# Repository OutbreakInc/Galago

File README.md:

Static sites are the fixies of the Internet.
      -Paul Graham, @paulg

Want to know how this works?  Fixie magic.

View the site here: [Logiblock.com](http://logiblock.com)

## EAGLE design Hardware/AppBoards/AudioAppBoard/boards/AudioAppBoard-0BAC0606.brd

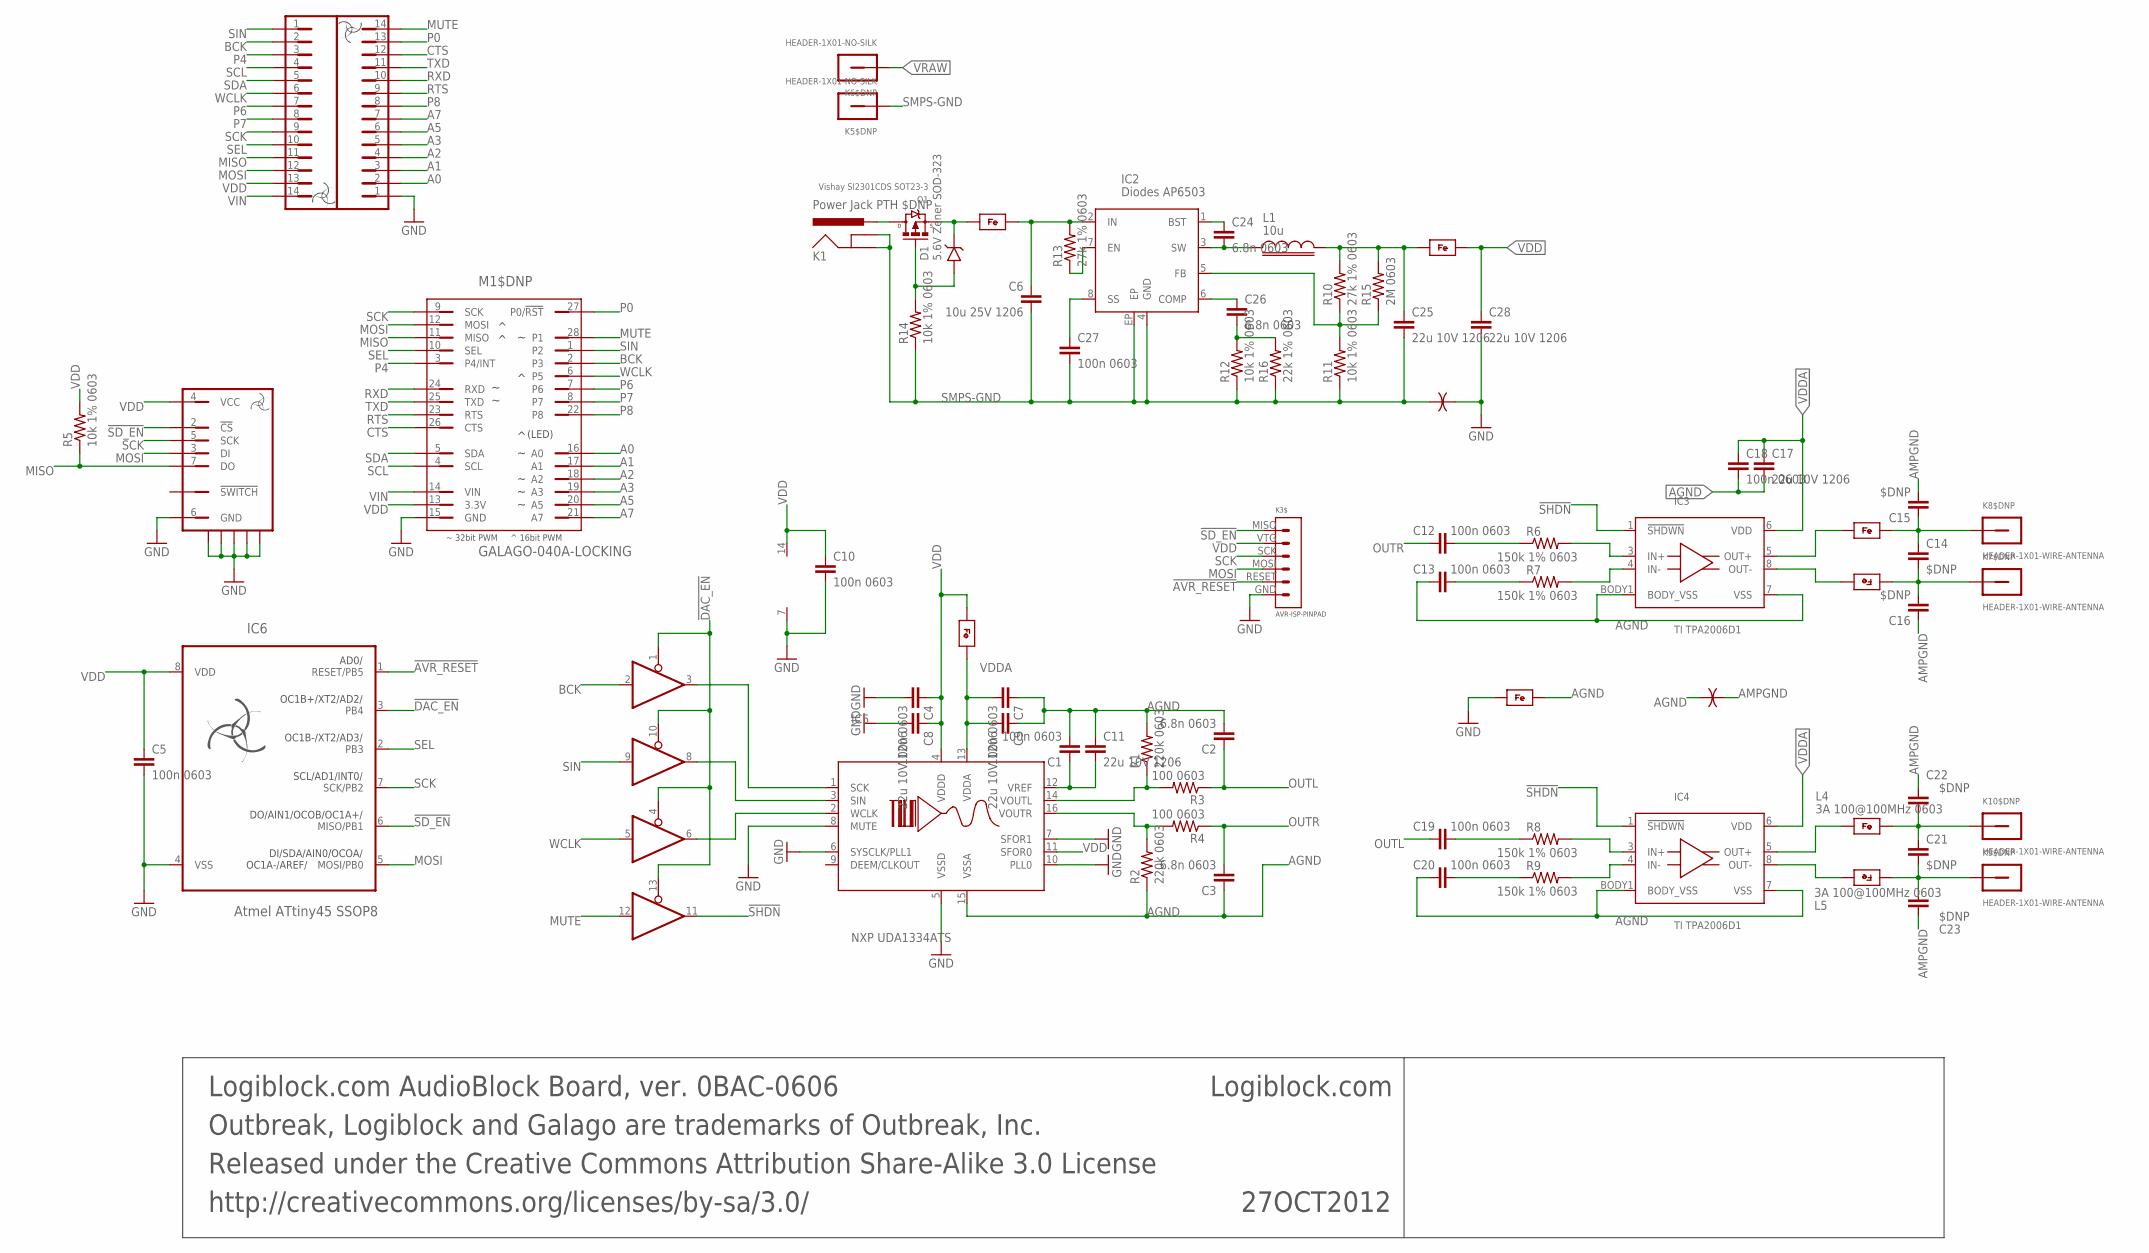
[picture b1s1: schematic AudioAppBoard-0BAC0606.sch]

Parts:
27OCT2012: Logiblock.com AudioBlock Board, ver. 0BAC-0606; INFO-BLOCK
C1, C4, C5, C7, C10: 100n 0603; 0603
C2, C3: 6.8n 0603; 0603
C6: 10u 25V 1206; 1206
C8, C9, C11, C17, C25, C28: 22u 10V 1206; 1206
C12, C13, C18, C19, C20, C27: 100n 0603; 0603-MIN
C14, C15, C16, C21, C22, C23: $DNP; 0603-MIN
C24, C26: 6.8n 0603; 0603-MIN
D1: 5.6V Zener SOD-323; SOD323
FB1, FB2, FB3: 3A 100@100MHz 0603; 0603
FB4: 3A 100@100MHz 0603; 0603-MIN
IC1: 74HC125-TSSOP14; TSSOP14
IC2: Diodes AP6503; EIAJ-SOIC8-3.9MM-EXPOSED-PAD
IC3, IC4: TI TPA2006D1; QFN8-3X3MM-TI-TPA200X
IC5: NXP UDA1334ATS; TSSOP16
IC6: Atmel ATtiny45 SSOP8; TSSOP8-4.4MM
K1: Power Jack PTH $DNP; POWER_JACK_PTH
K2: HIROSE-DM3D-SF-MICROSD; HIROSE-MICROSD-SOCKET-DM3D-SF
K2$DNP, K4$DNP: HEADER-1X14-NO-SILK-CHUNKY
K3$: AVR-ISP-PINPAD
K5$DNP, K6$DNP: HEADER-1X01-NO-SILK
K7$DNP, K8$DNP, K9$DNP, K10$DNP: HEADER-1X01-WIRE-ANTENNA
L1: 10u; INDUCTOR-SMD-6X6MM
L2, L3, L4, L5: 3A 100@100MHz 0603; 0603-MIN
M1$DNP: GALAGO-040A-LOCKING; GALAGO-LOCKING
Q1: Vishay SI2301CDS SOT23-3; SOT23-3
R1, R2: 220k 0603; 0603
R3, R4: 100 0603; 0603
R5, R11, R12, R14: 10k 1% 0603; 0603-MIN
R6, R7, R8, R9: 150k 1% 0603; 0603-MIN
R10, R13: 27k 1% 0603; 0603-MIN
R15: 2M 0603; 0603-MIN
R16: 22k 1% 0603; 0603-MIN
U1$, U2$: GND-ISOLATOR-0.008"

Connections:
!AVR_RESET: IC6.1 (RESET/PB5), K3$.RESET
!DAC_EN: IC1.1 (EN), IC1.4 (EN), IC1.10 (EN), IC1.13 (EN), IC6.3 (PB4)
!SD_EN: IC6.6 (MISO/PB1), K2.2 (!CS), K3$.MISO
!SHDN: IC1.11 (Y), IC3.1 (!SHDWN), IC4.1 (!SHDWN)
A0: K4$DNP.2, M1$DNP.16 (A0)
A1: K4$DNP.3, M1$DNP.17 (A1)
A2: K4$DNP.4, M1$DNP.18 (A2)
A3: K4$DNP.5, M1$DNP.19 (A3)
A5: K4$DNP.6, M1$DNP.20 (A5)
A7: K4$DNP.7, M1$DNP.21 (A7)
AGND: C1.1, C2.1, C3.2, C7.2, C9.2, C11.2, C13.2, C17.1, C18.1, C20.2, FB4.2, IC3.7 (VSS), IC3.BODY1 (BODY_VSS), IC4.7 (VSS), IC4.BODY1 (BODY_VSS), IC5.15 (VSSA), R1.2, R2.1, U2$.1 (A)
AMPGND: C15.1, C16.2, C22.1, C23.2, U2$.2 (B)
BCK: IC1.2 (A), K2$DNP.2, M1$DNP.2 (P3)
CTS: K4$DNP.12, M1$DNP.26 (CTS)
DAC_SCK: IC1.3 (Y), IC5.1 (SCK)
DAC_SIN: IC1.8 (Y), IC5.3 (SIN)
DAC_WCLK: IC1.6 (Y), IC5.2 (WCLK)
GND: C4.1, C5.1, C8.1, C10.1, C28.1, FB4.1, IC1.7 (VSS), IC5.5 (VSSD), IC5.6 (SYSCLK/PLL1), IC5.7 (SFOR1), IC5.8 (MUTE), IC5.10 (PLL0), IC6.4 (VSS), K2.6 (GND), K2.PP$1, K2.PP$2, K2.PP$3, K2.PP$4, K2.PP$5, K3$.GND, K4$DNP.1, M1$DNP.15 (GND), U1$.2 (B)
MISO: K2.7 (DO), K2$DNP.11, M1$DNP.11 (MISO), R5.1
MOSI: IC6.5 (MOSI/PB0), K2.3 (DI), K2$DNP.12, K3$.MOSI, M1$DNP.12 (MOSI)
MUTE: IC1.12 (A), K4$DNP.14, M1$DNP.28 (P1)
unnamed: C14.2, C15.2, K8$DNP.1, L2.2
unnamed: IC4.5 (OUT+), L4.1
unnamed: IC3.5 (OUT+), L2.1
unnamed: IC3.8 (OUT-), L3.2
unnamed: C12.1, R6.1
unnamed: D1.A, Q1.1 (GATE), R14.2
unnamed: C13.1, R7.1
unnamed: IC3.4 (IN-), R7.2
unnamed: IC3.3 (IN+), R6.2
unnamed: C14.1, C16.1, K7$DNP.1, L3.1
unnamed: IC4.8 (OUT-), L5.2
unnamed: C19.1, R8.1
unnamed: C20.1, R9.1
unnamed: IC4.4 (IN-), R9.2
unnamed: IC4.3 (IN+), R8.2
unnamed: C21.2, C22.2, K10$DNP.1, L4.2
unnamed: C21.1, C23.1, K9$DNP.1, L5.1
unnamed: D1.K, FB1.1, Q1.2 (SOURCE)
unnamed: C26.1, R12.2, R16.2
OUTL: C2.2, C19.2, R3.1
OUTR: C3.1, C12.2, R4.1
P0: K4$DNP.13, M1$DNP.27 (P0/!RST)
P4: K2$DNP.3, M1$DNP.3 (P4/INT)
P6: K2$DNP.7, M1$DNP.7 (P6)
P7: K2$DNP.8, M1$DNP.8 (P7)
P8: K4$DNP.8, M1$DNP.22 (P8)
RTS: K4$DNP.9, M1$DNP.23 (RTS)
RXD: K4$DNP.10, M1$DNP.24 (RXD)
SCK: IC6.7 (SCK/PB2), K2.5 (SCK), K2$DNP.9, K3$.SCK, M1$DNP.9 (SCK)
SCL: K2$DNP.4, M1$DNP.4 (SCL)
SDA: K2$DNP.5, M1$DNP.5 (SDA)
SEL: IC6.2 (PB3), K2$DNP.10, M1$DNP.10 (SEL)
SIN: IC1.9 (A), K2$DNP.1, M1$DNP.1 (P2)
SMPS-BST: C24.2, IC2.1 (BST)
SMPS-COMP: C26.2, IC2.6 (COMP)
SMPS-EN: IC2.7 (EN), R13.1
SMPS-FB: IC2.5 (FB), R10.1, R11.2, R15.1
SMPS-GND: C6.1, C25.1, C27.1, IC2.4 (GND), IC2.EP, K1.GND, K1.GNDBREAK, K5$DNP.1, R11.1, R12.1, R14.1, R16.1, U1$.1 (A)
SMPS-IN: C6.2, FB1.2, IC2.2 (IN), R13.2
SMPS-OUT: C25.2, FB2.1, L1.2, R10.2, R15.2
SMPS-SS: C27.2, IC2.8 (SS)
SMPS-SW: C24.1, IC2.3 (SW), L1.1
TXD: K4$DNP.11, M1$DNP.25 (TXD)
VDD: C4.2, C5.2, C8.2, C10.2, C28.2, FB2.2, FB3.1, IC1.14 (VDD), IC5.4 (VDDD), IC5.11 (SFOR0), IC6.8 (VDD), K2.4 (VCC), K2$DNP.13, K3$.VTG, M1$DNP.13 (3.3V), R5.2
VDDA: C7.1, C9.1, C17.2, C18.2, FB3.2, IC3.6 (VDD), IC4.6 (VDD), IC5.13 (VDDA)
VIN: K2$DNP.14, M1$DNP.14 (VIN)
VOUTL: IC5.14 (VOUTL), R1.1, R3.2
VOUTR: IC5.16 (VOUTR), R2.2, R4.2
VRAW: K1.PWR, K6$DNP.1, Q1.3 (DRAIN)
VREF: C1.2, C11.1, IC5.12 (VREF)
WCLK: IC1.5 (A), K2$DNP.6, M1$DNP.6 (P5)

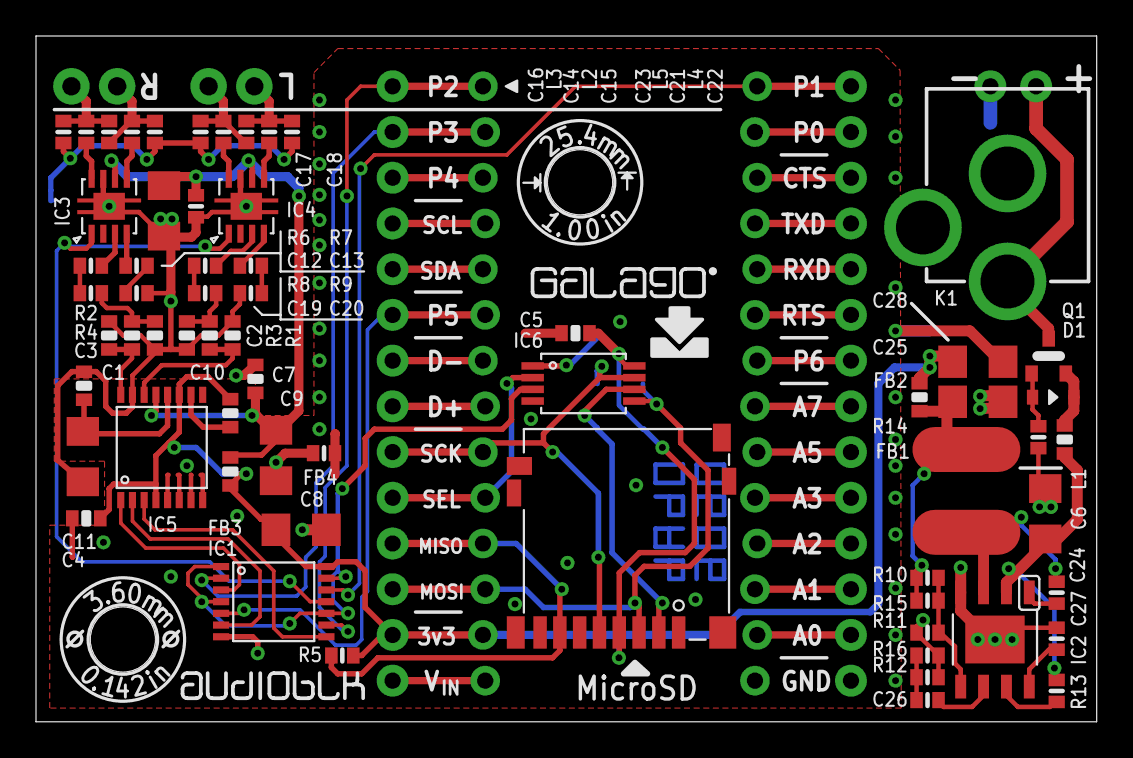
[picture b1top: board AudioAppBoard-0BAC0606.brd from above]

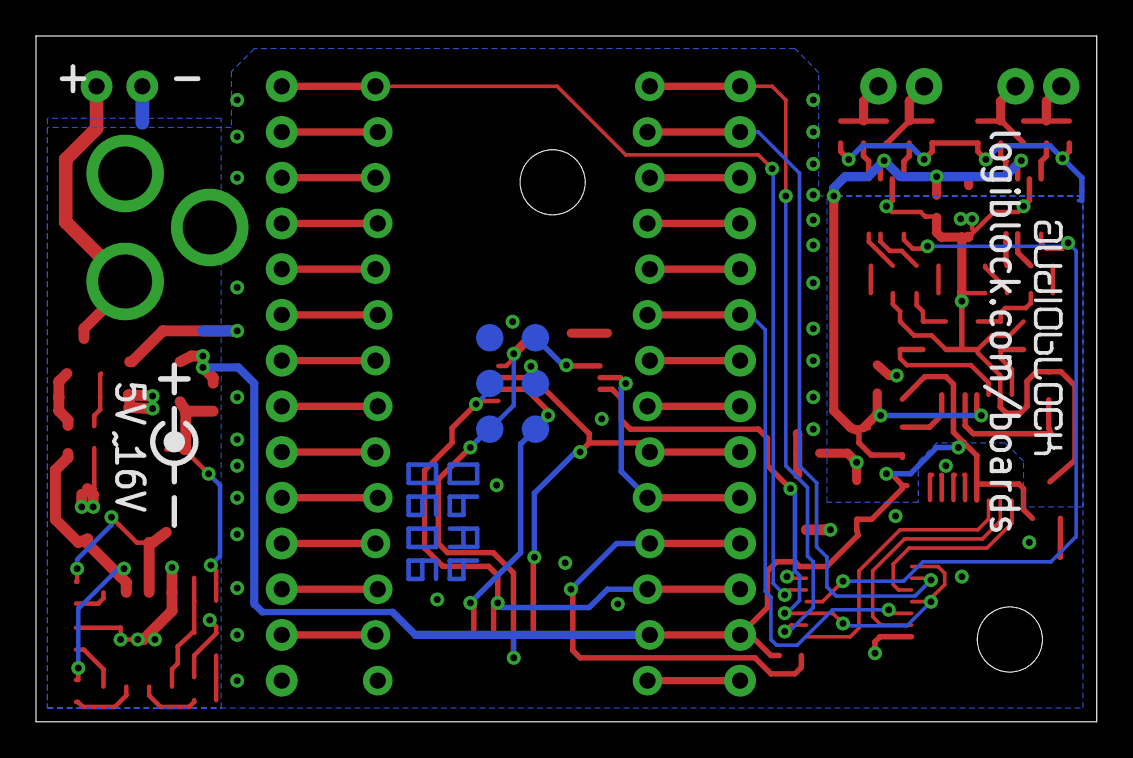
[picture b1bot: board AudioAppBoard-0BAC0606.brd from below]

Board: 2 copper layers, 58.9 x 38.1 mm, 80 parts (3 on the bottom side), 72 nets.

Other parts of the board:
U$1: GALAGO-LOGO
U$3: GALAGO-APP-BOARD-SYMBOL
U$10: MOUNTING-HOLE-3.6MM-LABELLED-DIAM
U$11: MOUNTING-HOLE-3.6MM-LABELLED-DISTANCE

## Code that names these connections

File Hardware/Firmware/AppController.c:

///////////////////////////////////////////////////////////////////////////////////////////


///////////////////////////////////////////////////////////////////////////////////////////

#include "AppController.h"

#include <avr/io.h>
#include <avr/interrupt.h>


#define PIN_SPI_SEL			PB3
#define PIN_SPI_SCK			PB2
#define PIN_SPI_MOSI		PB0

#define PINMASK_SPI_SEL		(1 << PIN_SPI_SEL)
#define PINMASK_SPI_SCK		(1 << PIN_SPI_SCK)
#define PINMASK_SPI_MOSI	(1 << PIN_SPI_MOSI)


//There are three reserved GXB addresses, used for stateless group addressing of all
//  unenumerated devices (0x00, 'probe address') and all enumerated devices
//  (0xFE, 'broadcast address').  Address 0xFF is reserved for communication robustness.

#define BUS_PROBE_ADDRESS		(0x00)
#define BUS_BROADCAST_ADDRESS	(0xFE)
#define BUS_RESERVED_ADDRESS	(0xFF)

///////////////////////////////////////////////////////////////////////////////////////////

u8		gSPIPseudovalue;

//Performs an SPI transaction (sends and receives a byte) in master mode
u8		SPIExchangeMaster(u8 byte)
{
	USIDR = byte;
	for(u8 i = 0; i < 8; i++)
	{
		USICR = 0x11;
		__asm__ volatile ("nop");
		__asm__ volatile ("nop");
		__asm__ volatile ("nop");
		USICR = 0x13;
	}
	return(USIDR);
}

//Setup or take down the SPI interface for a slave transfer
void	SPISetupSlave(void)
{
	gSPIPseudovalue = (gIOState & (1 << 1))? 0xFF : 0x00;
	USIDR = gSPIPseudovalue;
	USICR = 0x18;	//3-wire bus, external clock, shift on falling, read on rising edge, interrupt armed
}
void	SPIDisableSlave(void)
{
	USICR = 0x00;
}

u8		SPIExchangeSlave(u8 byte, u8 output)
{
	//only load the value if the pin is marked as output, else use the pseudovalue set in SPISetupSlave()
	USIDR = output? byte : gSPIPseudovalue;
	
	u8 out;
	
	//tricky - after 4 bits, fill the next 4 with the appropriate constant value to prevent output glitches
	USISR = 0xE8;
	while(!(USISR & 0x40));	//wait until USIOIF is 1
	
	out = USIDR;
	if(gIOState & (1 << 1))	USIDR |= 0x0F;
	else					USIDR &= ~0x0F;
	
	USISR = 0xE8;	//count another 8 edges
	while(!(USISR & 0x40));	//wait for the remaining 4 bits
	
	return(((out << 4) & 0xF0) | (USIDR & 0x0F));	//fuse the nibbles together
}


void	SPISetupGXB(void)
{
	//set up MOSI as a psuedo-open-drain shift register output
	DDRB &= ~PINMASK_SPI_MOSI;
	PORTB &= ~PINMASK_SPI_MOSI;
}

void	SPIDisableGXB(void)
{
	DDRB &= ~PINMASK_SPI_MOSI;
}

u8		SPIExchangeGXB(u8 byte)
{
	for(u8 bitIdx = 0; bitIdx < 8; bitIdx++)
	{
		while((PINB & PINMASK_SPI_SCK));	//wait while SCK is high
		
		//SCK now low, shift and open-drain-drive a bit
		if(byte & 0x80)
		{
			PORTB |= PINMASK_SPI_MOSI;
			DDRB |= PINMASK_SPI_MOSI;
			DDRB &= ~PINMASK_SPI_MOSI;	//release line for 1
			PORTB &= ~PINMASK_SPI_MOSI;
		}
		else
		{
			__asm__ volatile ("nop");
			__asm__ volatile ("nop");
			DDRB |= PINMASK_SPI_MOSI;	//sink line for 0
		}
		
		while(!(PINB & PINMASK_SPI_SCK));	//wait while SCK is low
		
		//SCK now high, check if there's a bus conflict
		if((byte & 0x80) && (!(PINB & PINMASK_SPI_MOSI)))	//if we're trying to drive a 1 (i.e. not sinking) and the line reads 0
			return(0);
		
		//no conflict, shift to next bit
		byte <<= 1;
	}
	
	while((PINB & PINMASK_SPI_SCK));	//wait while SCK is high on the final bit
	return(1);	//success!
}

void	SPIAckGXB(void)
{
	//ack bits are logic 0
	DDRB |= PINMASK_SPI_MOSI;	//sink line for 0
	PORTB &= ~PINMASK_SPI_MOSI;

	while(!(PINB & PINMASK_SPI_SCK));	//wait while SCK is low
	while((PINB & PINMASK_SPI_SCK));	//wait while SCK is high
	
	DDRB &= ~PINMASK_SPI_MOSI;
}


u8		ExchangeROM(void)
{
	SPISetupGXB();
	
	//length = the UUID, the length byte and all extra bytes described by the length byte
	u8 romLength = pgm_read_byte(kUUIDAndDescriptor + 16) + 16 + 1;
	
	for(u8 byteIdx = 0; byteIdx < romLength; byteIdx++)
		if(!SPIExchangeGXB(pgm_read_byte(kUUIDAndDescriptor + byteIdx)))
			return(0);	//bus collision
	
	//success!
	SPIDisableGXB();
	return(1);
}

//corrupts the stack in a specific way and jumps to core (like longjmp'ing back to core())
void	escape(void)
{
	__asm__ volatile
	(
		"eor	r1, r1		\n"
		"out	0x3f, r1	\n"
		"ldi	r28, 0x5F	\n"	//registers 0x3d:0x3e = 0x15f (initial stack value 0xff)
		"ldi	r29, 0x01	\n"
		"out	0x3e, r29	\n"
		"out	0x3d, r28	\n"
		"rcall	core		\n"
		"rcall	_exit		\n"
		::
	);
}

//handle a change on the SEL pin
ISR(PCINT0_vect)
{
	//on a falling edge, latch the new IO state and simply reboot.
	//  after booting, main() will put us back to sleep
	if(!(PINB & PINMASK_SPI_SEL))
	{
		//commit the new IO state
		PORTB = gIOState;
		DDRB = gIODir;
		
		escape();
	}
	//else do nothing but wake up
}

//our address
u8		gAddress;

void	init(void)
{
	gAddress = BUS_PROBE_ADDRESS;
	
	appInit();
	PORTB = gIOState;
	DDRB = gIODir;
}

//This is the special 32-bit key that, when sent to broadcast address 0xFE, de-enumerates all devices.
//  It's used to reset the bus from any state. 
u8 const kBusResetKey[4] PROGMEM =
{
	0xC1, 0x07, 0x27, 0x01
};

void	core(void)
{
	while(1)
	{
		sei();
		do
		{
			PCMSK |= PINMASK_SPI_SEL;	//interrupt when SEL changes
			GIFR = (1 << PCIF);			//reset SEL interrupt flag
			GIMSK |= (1 << PCIE);		//enable interrupt
			
			set_sleep_mode(SLEEP_MODE_IDLE);
			//we will wake when the SEL pin goes high again
			sleep_mode();
		}
		while(!(PINB & PINMASK_SPI_SEL));	//if SEL is 0, go back to sleep
		
		appReleaseBus();
		DDRB = gIODir;
		PORTB = gIOState;
		
		GIFR = (1 << PCIF);			//reset SEL interrupt flag
		
		SPISetupSlave();
		u8 addr = SPIExchangeSlave(0, 0);
		SPIDisableSlave();
		
		//if the address matches us - our address is initialized to the bus-probe address, so
		//  if we're not enumerated and the probe address is sent, respond to that
		if(addr == gAddress)
		{
			SPIAckGXB();
			if(addr == BUS_PROBE_ADDRESS)
			{
				//exchange the ROM.  If a bus conflict occurs, we're not the highest-ranking unaddressed
				//  device so wait for the next addressing cycle.
				if(ExchangeROM())
				{
					//we're in addressing mode so take an address assignment.
					SPISetupSlave();
					addr = SPIExchangeSlave(0, 0);
					SPIDisableSlave();
					SPIAckGXB();
					cli();	//disable interrupts until the outer loop repeats, so that we're hardened against race conditions
					
					if(addr < BUS_BROADCAST_ADDRESS)	//don't accept invalid addresses (0 is ok, becuase that unassigns us)
						gAddress = addr;
				}
				//else a bus conflict occurred
				
				//done with this cycle, go to sleep
			}
			else	//direct command
			{
				SPISetupSlave();
				u8 method = SPIExchangeSlave(0, 0);
				SPIAckGXB();
				if(method == 0xFF)
				{
					//de-enumerate from the bus
					gAddress = BUS_PROBE_ADDRESS;
				}
				else
					appCommand(method);
				SPIDisableSlave();
			}
		}
		else if(addr == BUS_BROADCAST_ADDRESS)
		{
			SPIAckGXB();
			SPISetupSlave();
			u8 match = 1;
			for(u8 i = 0; i < 4; i++)
			{
				match = match && (pgm_read_byte(kBusResetKey + i) == SPIExchangeSlave(0, 0));
				SPIAckGXB();
			}
			cli();	//harden against race conditions
			SPIDisableSlave();
			
			if(match)
				init();
			//we now return to the initial state, as if core() was called from main (or escape() was called)
		}
		//else go back to sleep
	}
}

int		main(void)
{
	init();	
	core();
}

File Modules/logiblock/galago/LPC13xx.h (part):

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	void		IRQ_Watchdog(void);
	void		IRQ_Brownout(void);
	void		IRQ_GPIO_3(void);	// Galago P6
	void		IRQ_GPIO_2(void);	// Galago SEL
	void		IRQ_GPIO_1(void);	// Galago A1 A2 A3 A5 RTS RXD TXD P2 P5 LED(/A6) A7
	void		IRQ_GPIO_0(void);	// Galago P0 P1 P3 P4 SCL SDA SCK CTS MISO MOSI A0
	
	#ifdef __cplusplus
	}	//extern "C"
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
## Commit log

2012-10-26 Add ArduinoShieldAdaptor-0BAC0803, AudioAppBoard-0BAC0603, BluetoothBoard-0BAC0702, EthernetAppBoard-0BAC0403, ExplorerBoard-0BAC0503, LEDAppBoard-0BAC0304
2012-10-26 Add build documents for ArduinoShieldAdaptor-0BAC0803, AudioAppBoard-0BAC0603, BluetoothBoard-0BAC0702, EthernetAppBoard-0BAC0403, ExplorerBoard-0BAC0503, LEDAppBoard-0BAC0304.
2012-10-26 add license and readme files
2012-10-26 improve readability of README.md
2012-10-26 add prototype photos and basic descriptions of five App Boards
2012-10-26 improve README
2012-10-26 improve README links
2012-10-26 improve README labels
2012-10-26 improve README introduction
2012-10-26 Add Outbreak-v0 library, Galago-0BAB040D with build docs and schematics
2012-10-27 Put a basic mounting hole back in the Arduino Shield Adaptor board which disappeared shortly before 0BAC0801 was spun.
2012-12-12 Updated Galago to version 0BAB0410, the first shipping version.
2013-03-11 bringing Etherblock to version 0404, Audioblock to 0606 and Shield Adapter to 0805.
2013-07-08 adding initial App Controller firmware for the five Galago App Boards that have it
2013-07-08 fixing late-night typos, all tested now
2013-07-09 changed GXB protocol such that downstream bytes are followed by a one-bit ack (logic 0). Testing shows it's solid, even in adverse conditions.
2013-07-09 fixed output glitch due to USI design - on the last falling edge an unexpected value could be output for up to one bit.
2013-07-10 Fixed #define typo in LED driver, 5 different units on one GXB bus works now. Woot!
2013-07-17 bringing in / organizing existing driver code into modules. Compiles correctly as of this commit, but these modules haven't been pushed to Moduleverse yet
2013-07-19 fixed command handling for nGPS_EN signal, discovered in testing final Explorer 0506 board
2013-07-21 rename s/AppBoards/AppBoard/
2013-07-21 rename timer-related definitions for consistency
2013-07-21 adding base AudioBlock module
2013-07-21 fixing component value typo for R6,R7,R8,R9 in AudioAppBoard-0BAC0606: should have been 150k 1% 0603 instead of 1.5k 1% 0603
2013-07-21 GalagoAPI: added preliminary task completion deferral - task callbacks are now called after wfi->active transition; bumped GalagoAPI version to 0.10.3; tweaks and continued development in AudioBlock 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
2013-07-23 implemented IanAber's suggestion for UART FIFO fix, fixes #6
2013-07-24 renamed s/shield-adapter/galago-shield-adapter/ for consistency
2013-08-08 updated all board firmware to version 2 to fix a subtle bug. v1 firmware was only deployed on some Etherblock boards where it had no effect anyway. Added IO::SPI::lock()/unlock() methods, fixed inter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
2013-08-08 Added LEDBlock module (logiblock/ledblock). Tested and working for simple examples
2013-08-13 added draft README for Ethernet board assembly
2013-08-13 updating etherblock photos and README
2013-08-15 Fixed image link on main README
2013-08-15 updated Audioblock to final image
2013-08-15 updated moduleverse publishing script
2013-08-15 added Galago photo and updated README
2013-08-15 adding StarterKit documentation
2013-08-28 added first-pass GalagoAPI documentation to GalagoAPI.h and removed one dead API method.
2013-08-28 docs touch-up to GalagoAPI.h.
2013-08-28 documentation++ in GalagoAPI.h.
2013-08-28 docs formatting tweaks in GalagoAPI.h.
2013-08-31 Add API docs link to main readme
2013-09-13 updates to Explorer module for final hardware, benign type changes in GalagoAPI
2013-09-13 added basic example projects
2013-09-15 fix typo that jammed up interrupts and tasks when acting on UART bytesAvailable()
2013-09-15 made bluetooth board example more interesting with bi-directional comms
2013-09-17 add gh-pages
2013-09-17 cleanup
2013-09-17 added README
2013-09-22 first draft of front page only
2013-09-23 building out rest of site, no template system yet
2013-09-23 roll back to temp cname
2013-09-23 simplifying, renaming and just starting on the IDE page. Duplicated code stinks, need handlebars or similar
2013-09-23 flipping the (very slow) switch from galago.co to logiblock.com
2013-09-23 added warning
2013-09-23 fixed price
2013-09-23 slowly building out galago page
2013-09-23 tweaked products/galago hero banner to DDD, gc
2013-09-23 tweaks
2013-09-24 experimental templating
2013-09-24 build script now adds built files to commit.
2013-09-24 updating build script
2013-09-24 updating IDE page
2013-09-24 updating build script, messing with IDE page
2013-09-24 testing
2013-09-24 css is now built by less; renamed docs to learn, added IDE link
2013-09-24 made breadcrumb generation a bit smarter, working on IDE page
2013-09-28 products page, product pages, app boards page and lots more
2013-09-28 made app board sketch image at the bottom of /index.html a link to /boards
2013-09-28 added learn/api/
2013-09-29 minor tweaks
2013-10-09 documentation fixups, added Galago debugger protocol documentation and tiny tweaks to AppBoard module to enable reading back UUIDs
2013-10-12 Adding demo firmware serializing/flashing scripts for App Boards
2013-11-28 Kamikaze site checkin. Also I have a stomachache
2013-11-28 readmead
2013-11-28 fixed ide link
2013-11-28 need a better cookie workaround
2013-11-29 added orphan payment-related method
2013-12-06 availability tweak, API isn't ready yet
2013-12-08 Building initial cart functionality
2013-12-08 Cart functionality
2013-12-09 Working on frontend store and cart functionality
2013-12-09 Fixed context problem with local cookies (forgot about the path attribute) and removed state.html and iframe
2013-12-09 Fixing cookie bugs
2014-01-06 As promised, released debugger firmware for the ATtiny on Galago-compatible products.
2014-02-25 Made blog template
2014-03-10 Improved Explorer board example to work with final explorer API (previously only worked with beta API.)
2014-03-10 Added pin name annotations to LPC13xx header GPIO pin events.
2014-03-10 Added crucial clarification to the Explorer module API. Still needs more
2014-03-10 AVR chips need a little while (64ms + 16000 clocks) to wake up. The App Board usage policy must require about 80ms warm-up time for those chips.
2015-06-17 Site WIP
2015-06-22 New site content
2015-08-12 Added public images
2016-02-24 Added CV
